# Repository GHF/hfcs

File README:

hfcs - firmware for High Fructose
====
Xo Wang (http://www.geekshavefeelings.com)

About
-----
:D

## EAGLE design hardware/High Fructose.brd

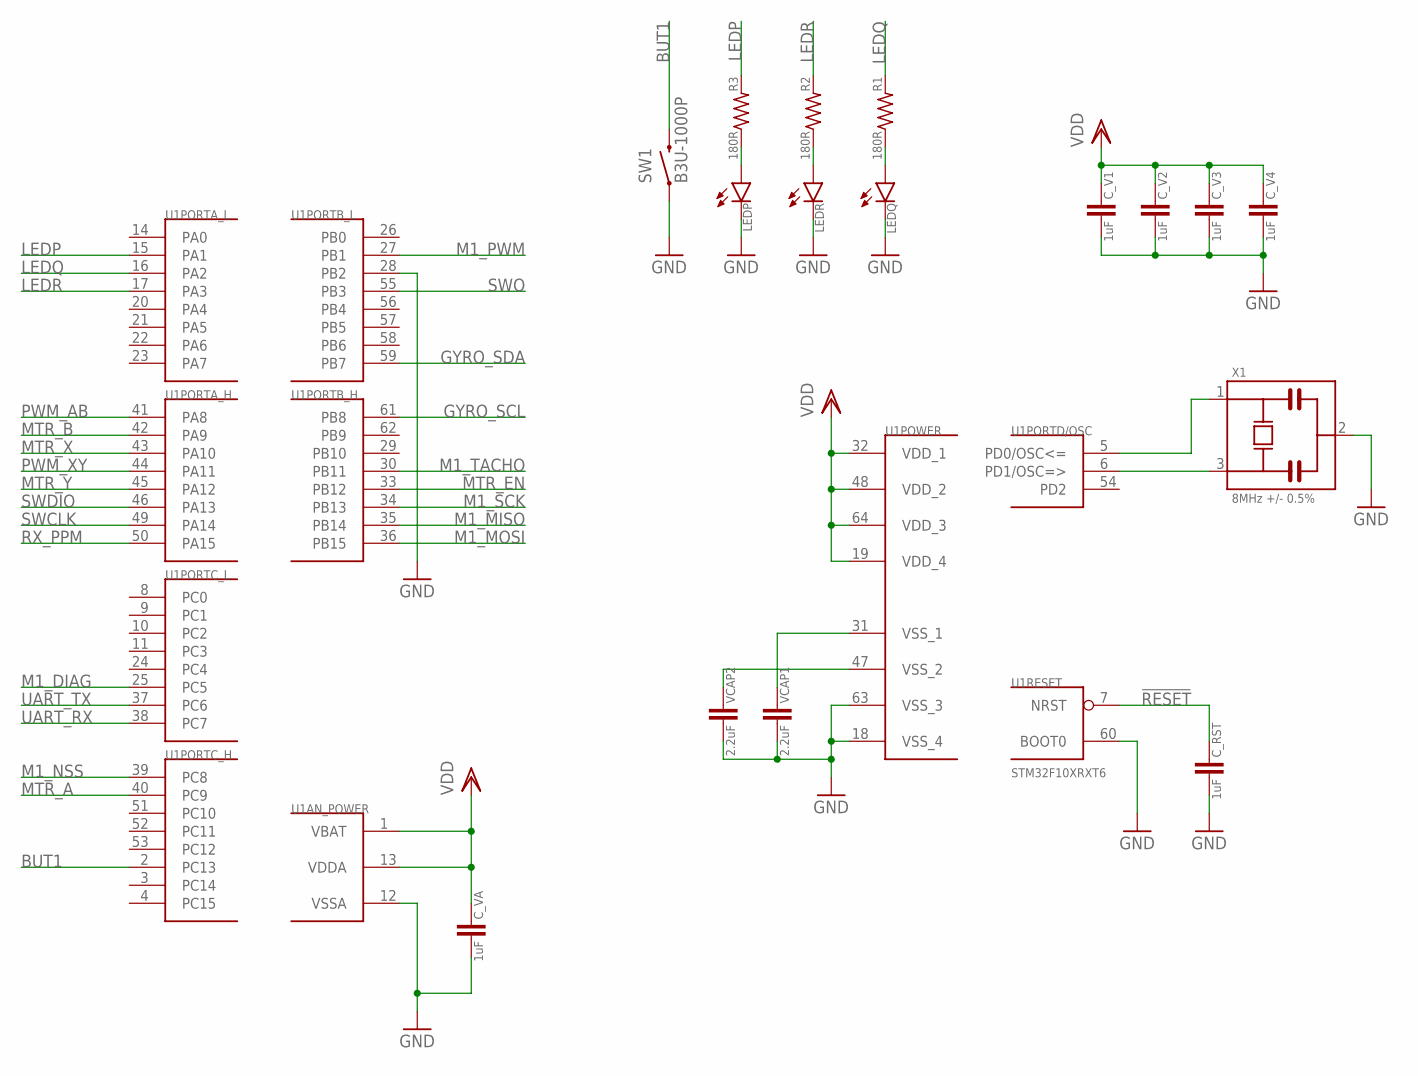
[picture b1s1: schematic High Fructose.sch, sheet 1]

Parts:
C_RST: 1uF; 0603
C_V1, C_V2, C_V3, C_V4: 1uF; 0603
C_VA: 1uF; 0603
LEDP: LED0805; 0805_POL
LEDQ: LED0805; 0805_POL
LEDR: LED0805; 0805_POL
R1, R2, R3: 180R; 0603
SW1: B3U-1000P
U1: STM32F10XRXT6; TQFP64
VCAP1, VCAP2: 2.2uF; 0603
X1: 8MHz +/- 0.5%; MURATA_CSTCE

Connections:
!RESET: C_RST.1, U1.7 (NRST); also elsewhere on the board
BUT1: SW1.2, U1.2 (PC13)
GND: C_RST.2, C_V1.2, C_V2.2, C_V3.2, C_V4.2, C_VA.2, LEDP.- (C), LEDQ.- (C), LEDR.- (C), SW1.1, U1.12 (VSSA), U1.18 (VSS_4), U1.28 (PB2), U1.60 (BOOT0), U1.63 (VSS_3), VCAP1.2, VCAP2.2, X1.2; also elsewhere on the board
GYRO_SCL: U1.61 (PB8); also elsewhere on the board
GYRO_SDA: U1.59 (PB7); also elsewhere on the board
LEDP: R3.2, U1.15 (PA1)
LEDQ: R1.2, U1.16 (PA2)
LEDR: R2.2, U1.17 (PA3)
M1_DIAG: U1.25 (PC5); also elsewhere on the board
M1_MISO: U1.35 (PB14); also elsewhere on the board
M1_MOSI: U1.36 (PB15); also elsewhere on the board
M1_NSS: U1.39 (PC8); also elsewhere on the board
M1_PWM: U1.27 (PB1); also elsewhere on the board
M1_SCK: U1.34 (PB13); also elsewhere on the board
M1_TACHO: U1.30 (PB11); also elsewhere on the board
MTR_A: U1.40 (PC9); also elsewhere on the board
MTR_B: U1.42 (PA9); also elsewhere on the board
MTR_EN: U1.33 (PB12); also elsewhere on the board
MTR_X: U1.43 (PA10); also elsewhere on the board
MTR_Y: U1.45 (PA12); also elsewhere on the board
unnamed: U1.6 (PD1/OSC=>), X1.3
unnamed: U1.5 (PD0/OSC<=), X1.1
unnamed: U1.47 (VSS_2), VCAP2.1
unnamed: U1.31 (VSS_1), VCAP1.1
unnamed: LEDQ.+ (A), R1.1
unnamed: LEDP.+ (A), R3.1
unnamed: LEDR.+ (A), R2.1
PWM_AB: U1.41 (PA8); also elsewhere on the board
PWM_XY: U1.44 (PA11); also elsewhere on the board
RX_PPM: U1.50 (PA15); also elsewhere on the board
SWCLK: U1.49 (PA14); also elsewhere on the board
SWDIO: U1.46 (PA13); also elsewhere on the board
SWO: U1.55 (PB3); also elsewhere on the board
UART_RX: U1.38 (PC7); also elsewhere on the board
UART_TX: U1.37 (PC6); also elsewhere on the board
VDD: C_V1.1, C_V2.1, C_V3.1, C_V4.1, C_VA.1, U1.1 (VBAT), U1.13 (VDDA), U1.19 (VDD_4), U1.32 (VDD_1), U1.48 (VDD_2), U1.64 (VDD_3); also elsewhere on the board

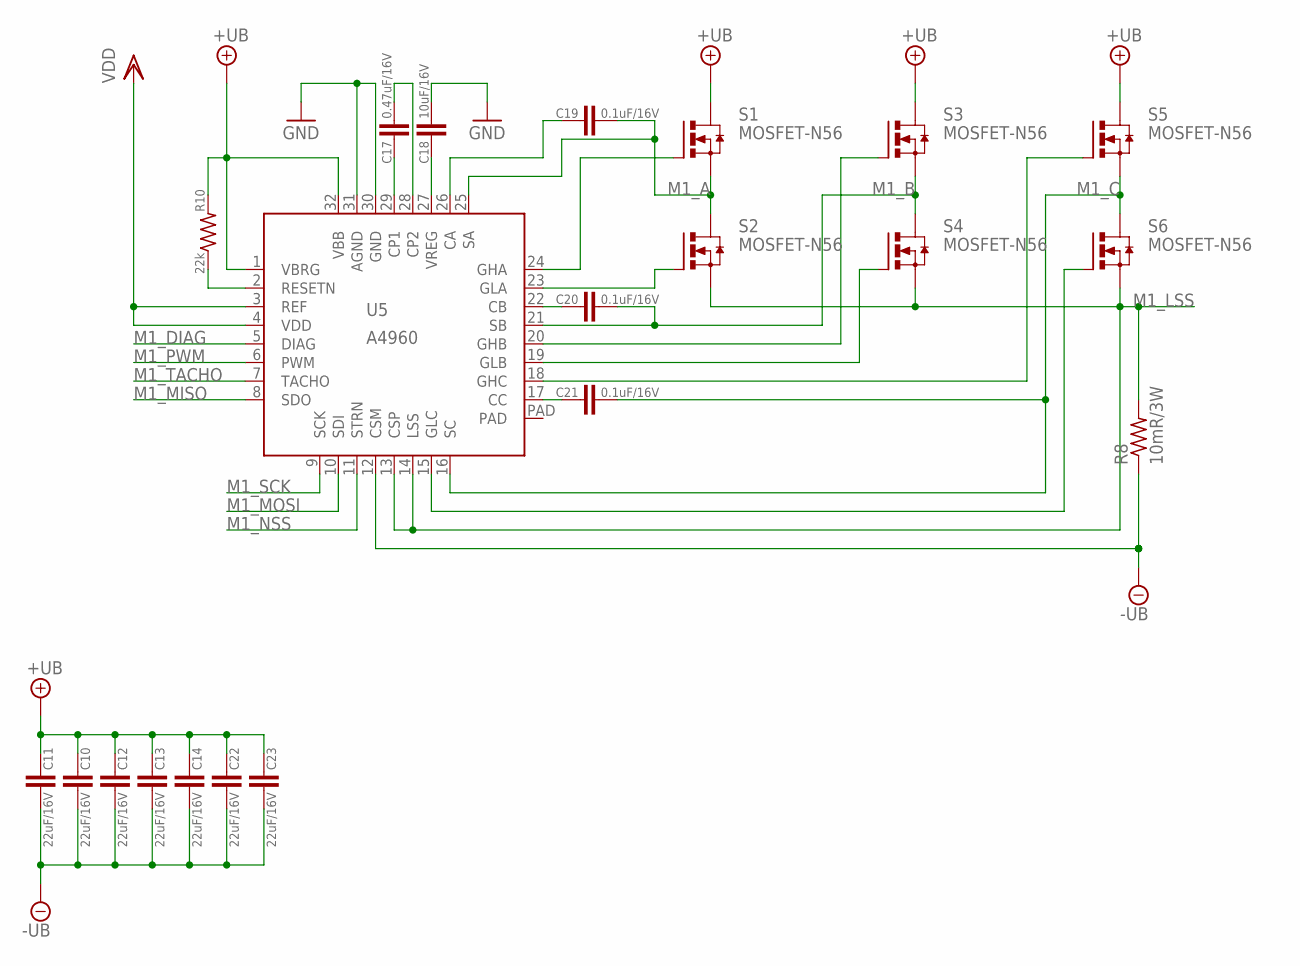
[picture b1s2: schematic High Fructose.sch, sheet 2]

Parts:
C10, C11, C12, C13, C14, C22, C23: 22uF/16V; 1206
C17: 0.47uF/16V; 0603
C18: 10uF/16V; 0805
C19, C20, C21: 0.1uF/16V; 0603
R8: 10mR/3W; R2512
R10: 22k; 0603
S1, S2, S3, S4, S5, S6: MOSFET-N56; SON-5X6
U5: A4960; LQFP32-THERMPAD

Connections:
+UB: C10.1, C11.1, C12.1, C13.1, C14.1, C22.1, C23.1, R10.2, S1.D, S3.D, S5.D, U5.1 (VBRG), U5.32 (VBB)
-UB: C10.2, C11.2, C12.2, C13.2, C14.2, C22.2, C23.2, R8.1, U5.12 (CSM)
GND: C18.2, U5.30 (GND), U5.31 (AGND); also elsewhere on the board
M1_A: C19.2, S1.S1 (S), S1.S2 (S), S1.S3 (S), S2.D, U5.25 (SA)
M1_B: C20.2, S3.S1 (S), S3.S2 (S), S3.S3 (S), S4.D, U5.21 (SB)
M1_C: C21.2, S5.S1 (S), S5.S2 (S), S5.S3 (S), S6.D, U5.16 (SC)
M1_DIAG: U5.5 (DIAG); also elsewhere on the board
M1_LSS: R8.2, S2.S1 (S), S2.S2 (S), S2.S3 (S), S4.S1 (S), S4.S2 (S), S4.S3 (S), S6.S1 (S), S6.S2 (S), S6.S3 (S), U5.13 (CSP), U5.14 (LSS)
M1_MISO: U5.8 (SDO); also elsewhere on the board
M1_MOSI: U5.10 (SDI); also elsewhere on the board
M1_NSS: U5.11 (STRN); also elsewhere on the board
M1_PWM: U5.6 (PWM); also elsewhere on the board
M1_SCK: U5.9 (SCK); also elsewhere on the board
M1_TACHO: U5.7 (TACHO); also elsewhere on the board
unnamed: C17.1, U5.29 (CP1)
unnamed: C17.2, U5.28 (CP2)
unnamed: C18.1, U5.27 (VREG)
unnamed: S1.G, U5.24 (GHA)
unnamed: S2.G, U5.23 (GLA)
unnamed: C19.1, U5.26 (CA)
unnamed: S3.G, U5.20 (GHB)
unnamed: S4.G, U5.19 (GLB)
unnamed: C20.1, U5.22 (CB)
unnamed: S5.G, U5.18 (GHC)
unnamed: S6.G, U5.15 (GLC)
unnamed: C21.1, U5.17 (CC)
unnamed: R10.1, U5.2 (RESETN)
VDD: U5.3 (REF), U5.4 (VDD); also elsewhere on the board

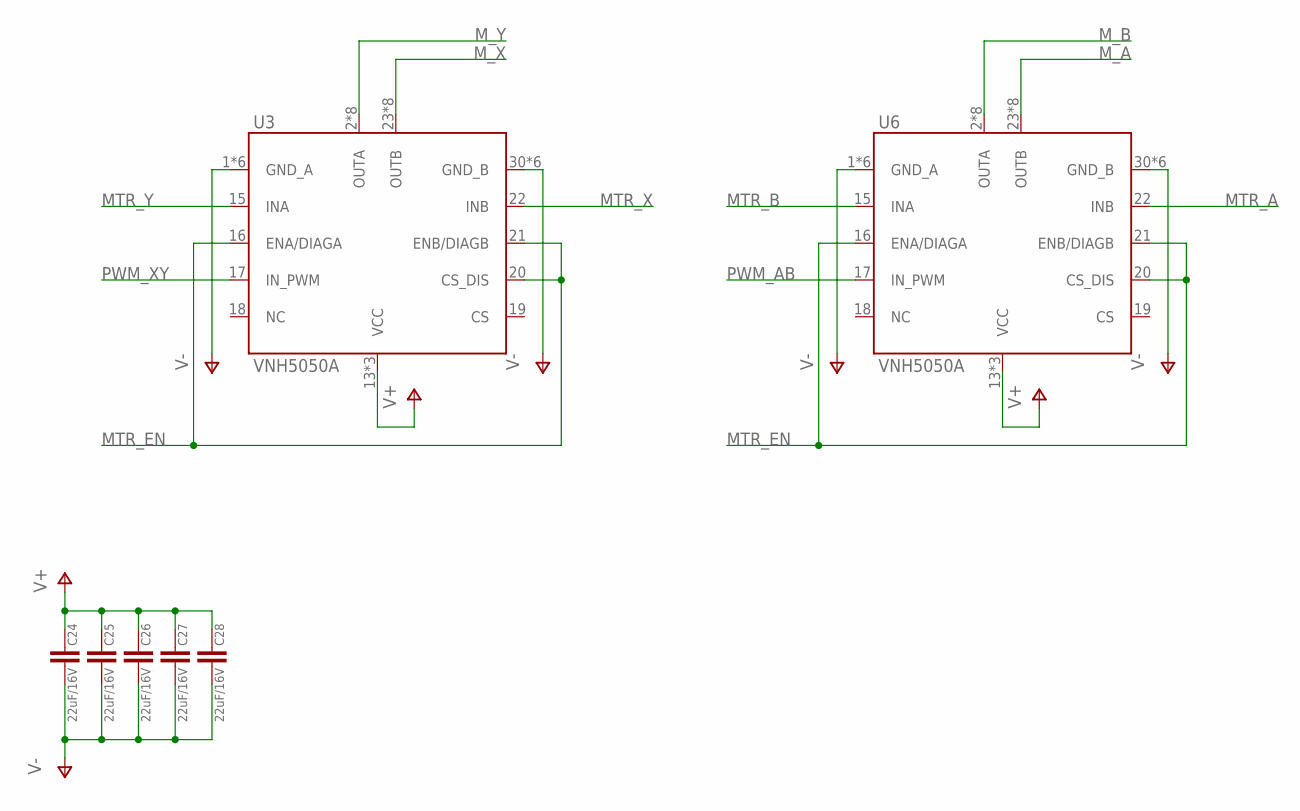
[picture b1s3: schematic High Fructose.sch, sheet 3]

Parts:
C24, C25, C26, C27, C28: 22uF/16V; 1206
U3, U6: VNH5050A; POWERSSO-36

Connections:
MTR_A: U6.22 (INB); also elsewhere on the board
MTR_B: U6.15 (INA); also elsewhere on the board
MTR_EN: U3.16 (ENA/DIAGA), U3.20 (CS_DIS), U3.21 (ENB/DIAGB), U6.16 (ENA/DIAGA), U6.20 (CS_DIS), U6.21 (ENB/DIAGB); also elsewhere on the board
MTR_X: U3.22 (INB); also elsewhere on the board
MTR_Y: U3.15 (INA); also elsewhere on the board
M_A: U6.23 (OUTB), U6.25 (OUTB), U6.26 (OUTB), U6.27 (OUTB), U6.28 (OUTB), U6.29 (OUTB), U6.35 (OUTB), U6.LS_B (OUTB)
M_B: U6.2 (OUTA), U6.8 (OUTA), U6.9 (OUTA), U6.10 (OUTA), U6.11 (OUTA), U6.12 (OUTA), U6.14 (OUTA), U6.LS_A (OUTA)
M_X: U3.23 (OUTB), U3.25 (OUTB), U3.26 (OUTB), U3.27 (OUTB), U3.28 (OUTB), U3.29 (OUTB), U3.35 (OUTB), U3.LS_B (OUTB)
M_Y: U3.2 (OUTA), U3.8 (OUTA), U3.9 (OUTA), U3.10 (OUTA), U3.11 (OUTA), U3.12 (OUTA), U3.14 (OUTA), U3.LS_A (OUTA)
PWM_AB: U6.17 (IN_PWM); also elsewhere on the board
PWM_XY: U3.17 (IN_PWM); also elsewhere on the board
V+: C24.1, C25.1, C26.1, C27.1, C28.1, U3.13 (VCC), U3.24 (VCC), U3.HS_AB (VCC), U6.13 (VCC), U6.24 (VCC), U6.HS_AB (VCC); also elsewhere on the board
V-: C24.2, C25.2, C26.2, C27.2, C28.2, U3.1 (GND_A), U3.3 (GND_A), U3.4 (GND_A), U3.5 (GND_A), U3.6 (GND_A), U3.7 (GND_A), U3.30 (GND_B), U3.31 (GND_B), U3.32 (GND_B), U3.33 (GND_B), U3.34 (GND_B), U3.36 (GND_B), U6.1 (GND_A), U6.3 (GND_A), U6.4 (GND_A), U6.5 (GND_A), U6.6 (GND_A), U6.7 (GND_A), U6.30 (GND_B), U6.31 (GND_B), U6.32 (GND_B), U6.33 (GND_B), U6.34 (GND_B), U6.36 (GND_B); also elsewhere on the board

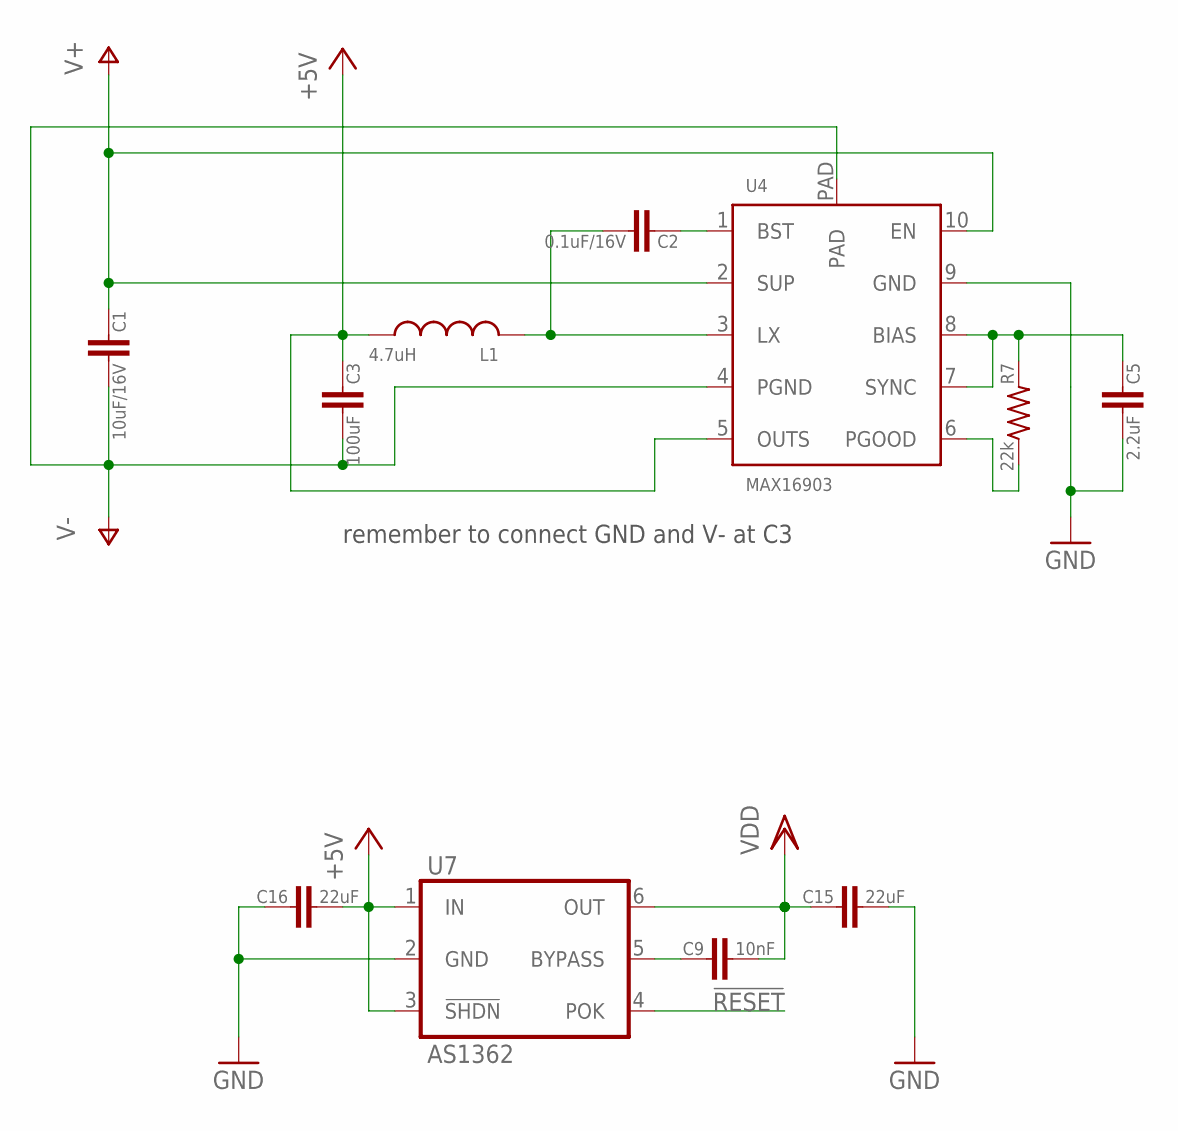
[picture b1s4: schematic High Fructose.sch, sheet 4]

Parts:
C1: 10uF/16V; 0805
C2: 0.1uF/16V; 0603
C3: 100uF; 1206
C5: 2.2uF; 0603
C9: 10nF; 0603
C15, C16: 22uF; 0805
L1: 4.7uH; TAIYO-YUDEN_NR30
R7: 22k; 0603
U4: MAX16903; TDFN-10
U7: AS1362; SOT23-6

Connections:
!RESET: U7.4 (POK); also elsewhere on the board
+5V: C3.1, C16.2, L1.1, U4.5 (OUTS), U7.1 (IN), U7.3 (!SHDN); also elsewhere on the board
GND: C5.2, C15.2, C16.1, U4.9 (GND), U7.2 (GND); also elsewhere on the board
unnamed: C2.1, U4.1 (BST)
unnamed: C9.1, U7.5 (BYPASS)
unnamed: C2.2, L1.2, U4.3 (LX)
unnamed: C5.1, R7.2, U4.7 (SYNC), U4.8 (BIAS)
unnamed: R7.1, U4.6 (PGOOD)
V+: C1.1, U4.2 (SUP), U4.10 (EN); also elsewhere on the board
V-: C1.2, C3.2, U4.4 (PGND), U4.PAD; also elsewhere on the board
VDD: C9.2, C15.1, U7.6 (OUT); also elsewhere on the board

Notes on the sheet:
remember to connect GND and V- at C3

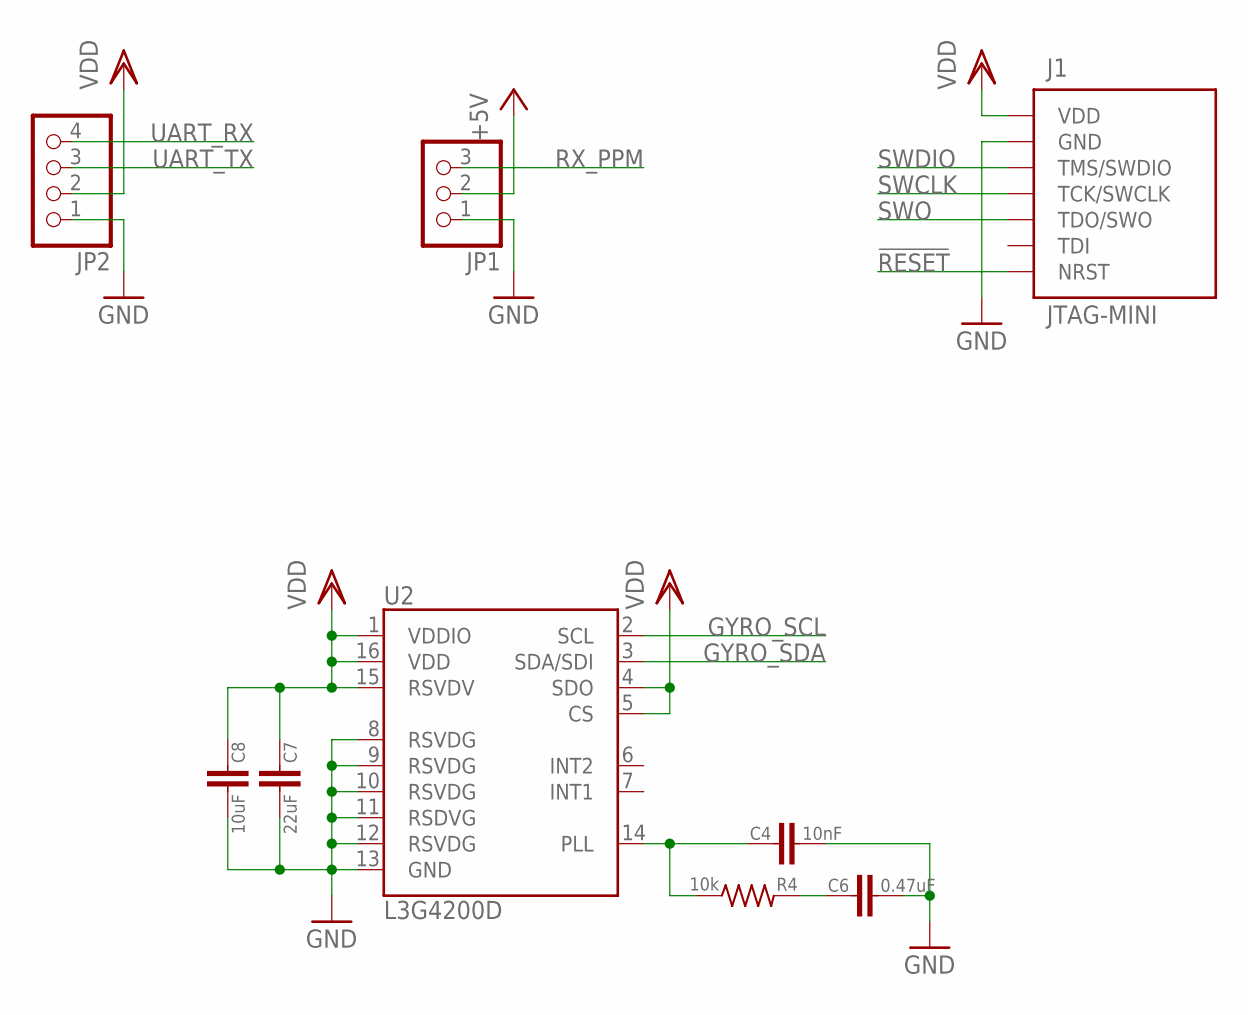
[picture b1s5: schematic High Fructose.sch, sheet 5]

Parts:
C4: 10nF; 0603
C6: 0.47uF; 0603
C7: 22uF; 0805
C8: 10uF; 0603
J1: JTAG-MINI
JP1: PINHD-1X03_2.54-S; 1X03-S
JP2: PINHD-1X04_2.54-S; 1X04-S
R4: 10k; 0603
U2: L3G4200D; LGA16-4X4

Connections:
!RESET: J1.NRST; also elsewhere on the board
+5V: JP1.2; also elsewhere on the board
GND: C4.2, C6.2, C7.2, C8.2, J1.GND1 (GND), J1.GND2 (GND), J1.GND3 (GND), J1.GND4 (GND), JP1.1, JP2.1, U2.8 (RSVDG), U2.9 (RSVDG), U2.10 (RSVDG), U2.11 (RSDVG), U2.12 (RSVDG), U2.13 (GND); also elsewhere on the board
GYRO_SCL: U2.2 (SCL); also elsewhere on the board
GYRO_SDA: U2.3 (SDA/SDI); also elsewhere on the board
unnamed: C4.1, R4.1, U2.14 (PLL)
unnamed: C6.1, R4.2
RX_PPM: JP1.3; also elsewhere on the board
SWCLK: J1.TCK (TCK/SWCLK); also elsewhere on the board
SWDIO: J1.TMS (TMS/SWDIO); also elsewhere on the board
SWO: J1.TDO (TDO/SWO); also elsewhere on the board
UART_RX: JP2.4; also elsewhere on the board
UART_TX: JP2.3; also elsewhere on the board
VDD: C7.1, C8.1, J1.VDD, JP2.2, U2.1 (VDDIO), U2.4 (SDO), U2.5 (CS), U2.15 (RSVDV), U2.16 (VDD); also elsewhere on the board

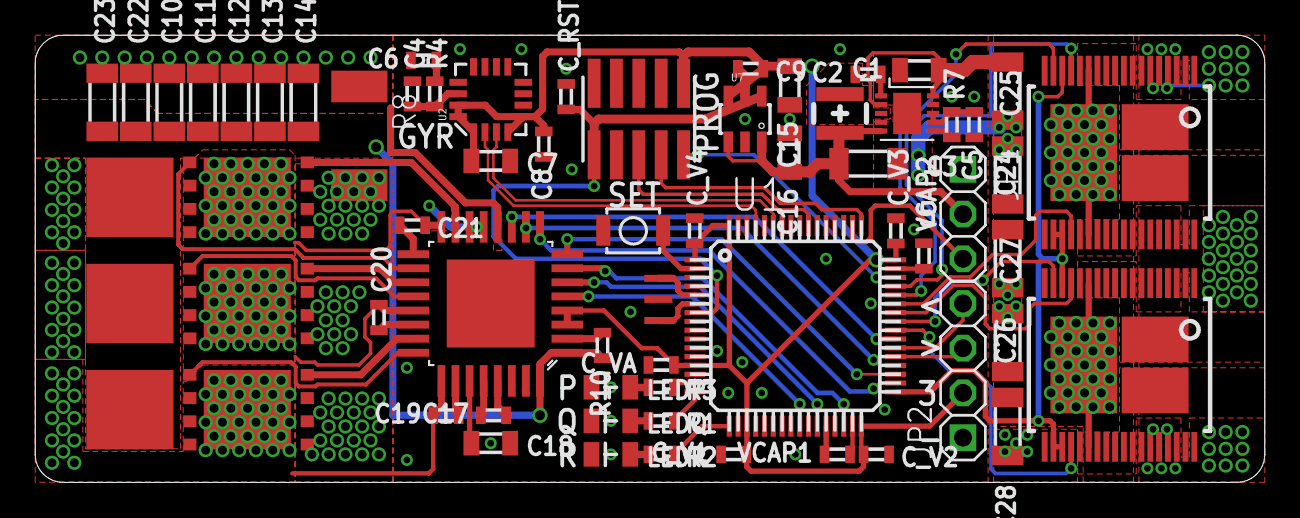
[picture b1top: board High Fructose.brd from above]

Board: 2 copper layers, 69.8 x 25.4 mm, 65 parts (0 on the bottom side), 69 nets.

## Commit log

2013-02-08 Importing Gyro King code and latest ChibiOS 2.4.x
2013-02-09 Set up project for High Fructose
2013-02-10 Add VNH5050A drivers, fix some minor issues
2013-02-10 Change RX_PPM to pulldown (from pullup)
2013-02-15 Implement input processing loop
2013-02-17 Add deadband range mapping and fix Makefile
2013-02-17 Change C++ standard from gnu++0x to c++11, explicitly disable exceptions
2013-02-17 Update hardware dir with High Fructose
2013-02-20 Remove -fno-exceptions because it breaks debugging somehow
2013-08-13 Change A4960 settings (including reduce ridiculous phase advance)
2013-08-13 Ignore A4960 fault signal; tighten up failsafe loop
2013-08-14 Optimize nabs (negative absolute value) function
2013-08-20 Update average function with overflow-safe round-to-zero version
2013-08-21 Document mapRanges function
2013-08-21 Add code to read L3GD20 gyro
2013-08-21 Use LEDR as main loop duty cycle indicator
2013-08-22 Clean up L3GD20, add error flag set by I2C comm errors
2013-08-22 Separate motor control into functions based on failsafe state and gyro enable state
2013-08-22 Add PID library and glue code
2013-08-22 Add gyro bias recording to initialization
2013-08-22 Add and tune gyro z-axis control, tighten loop to 200Hz, and add deadband for motor PWM
2013-08-22 Fix missing source file in Makefile
2013-08-24 Add -std=c++11 to Eclipse discovery options to index C++11 headers correctly
2013-08-24 Add warnings and -Werror to build options

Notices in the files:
parts and their libraries:
SparkFun-Sensors: Licensing: CC v3.0 Share-Alike You are welcome to use this library for commercial purposes.
